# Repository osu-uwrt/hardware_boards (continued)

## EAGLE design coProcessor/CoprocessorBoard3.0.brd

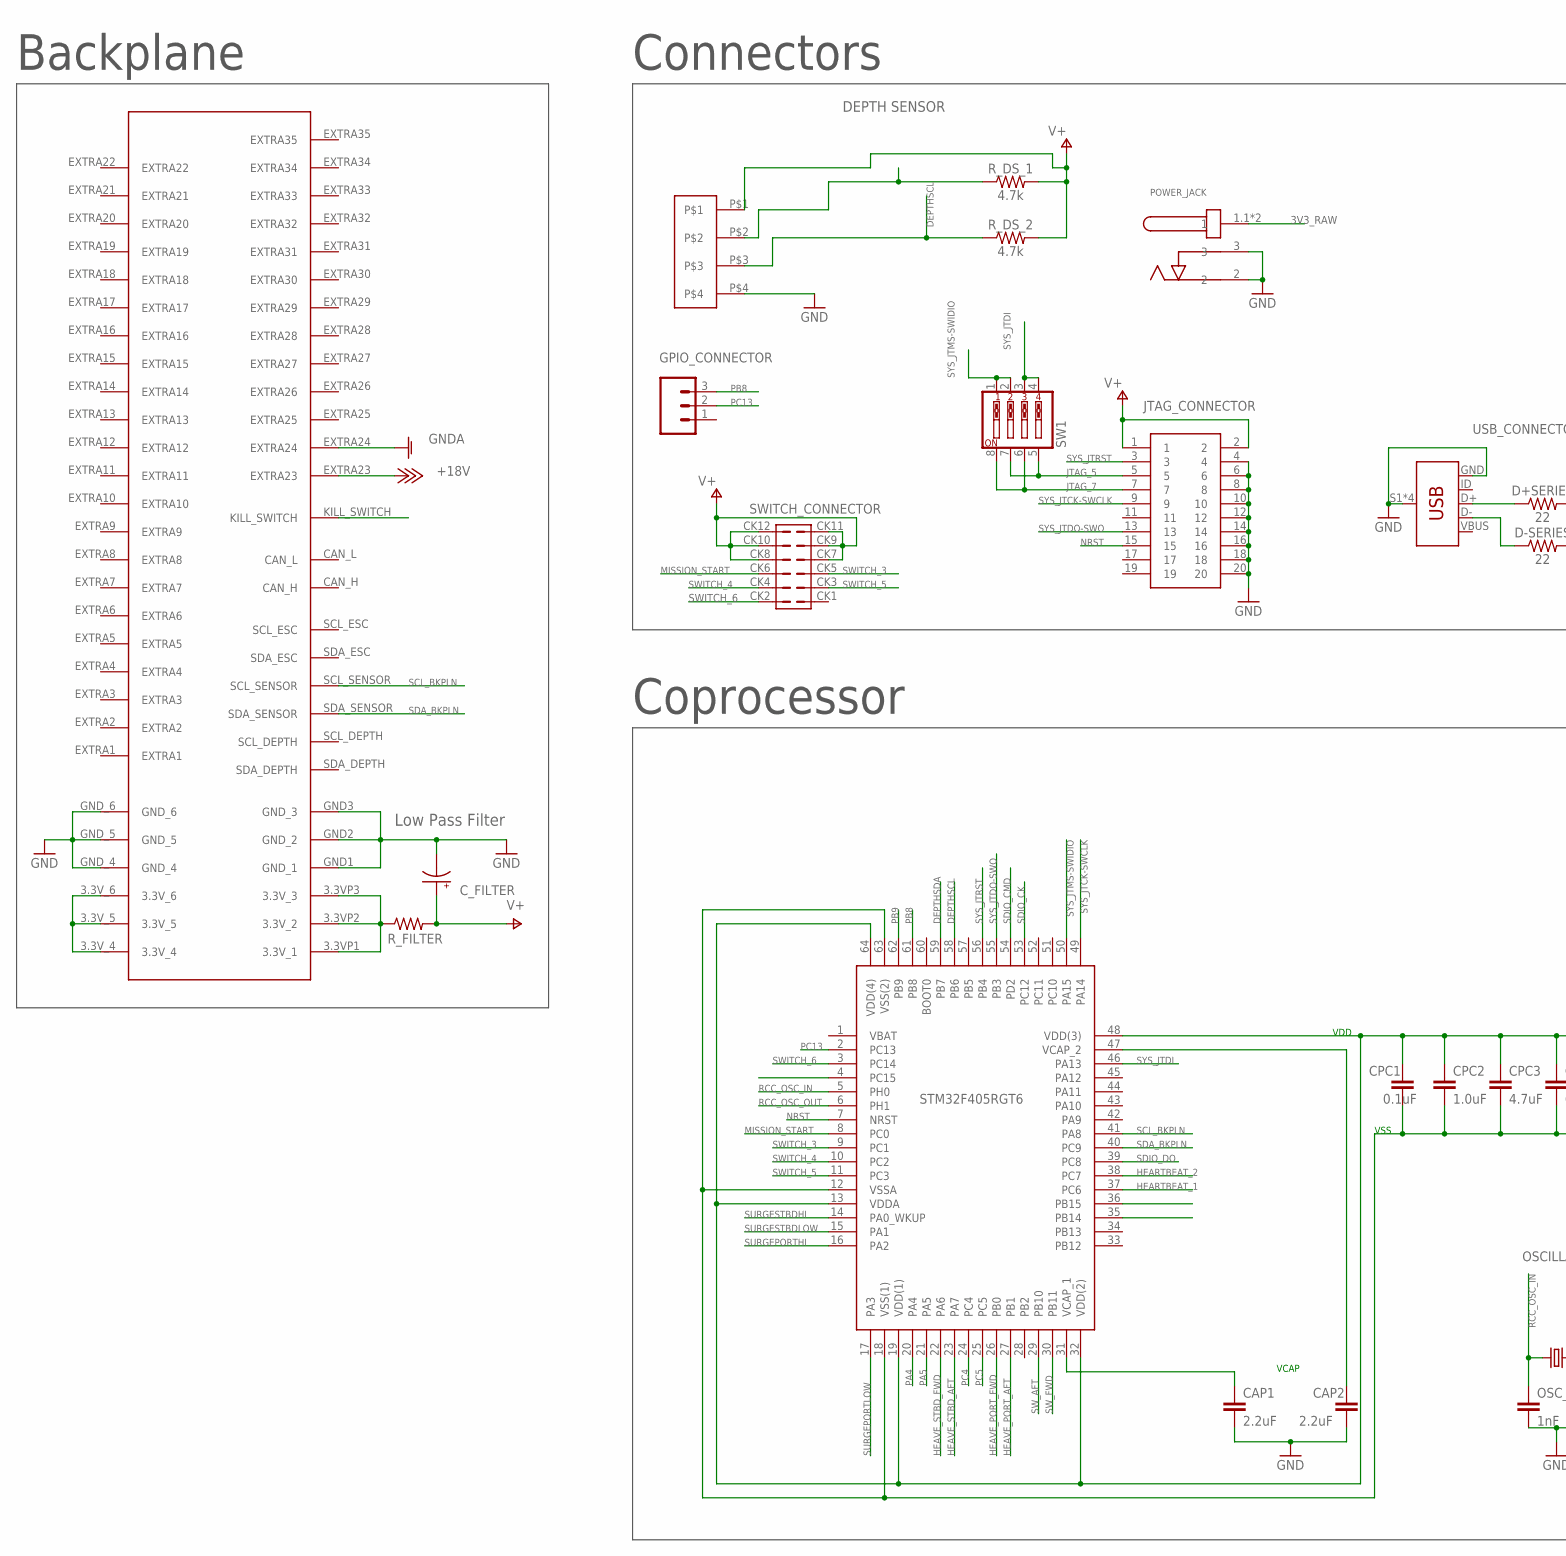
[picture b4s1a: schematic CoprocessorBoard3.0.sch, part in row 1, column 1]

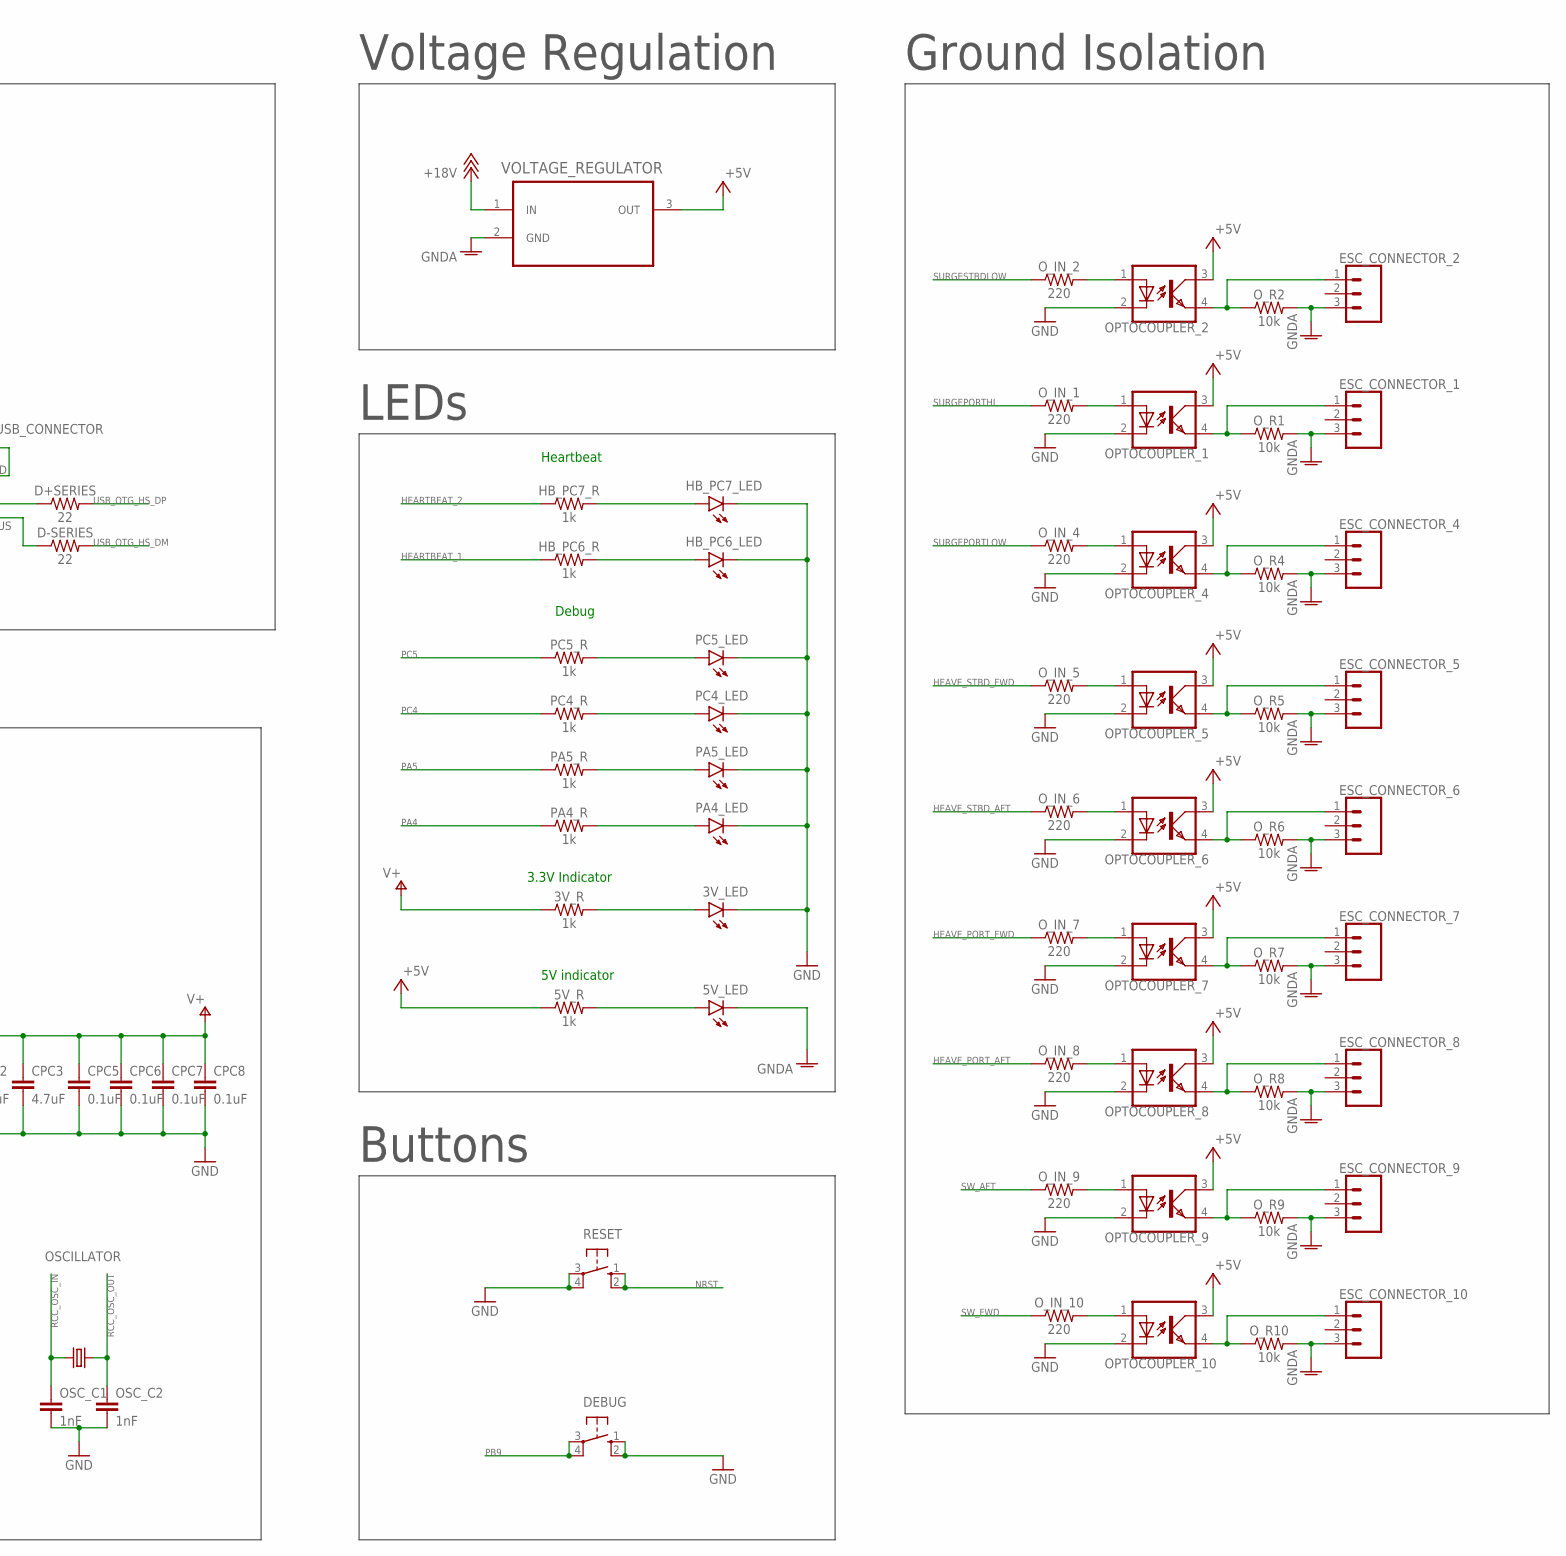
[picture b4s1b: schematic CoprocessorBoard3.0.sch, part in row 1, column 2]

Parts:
3V_LED, 5V_LED: WHITE; LED-0603
3V_R, 5V_R: 1k; AXIAL-0.3
CAP1, CAP2: 2.2uF; 0603
CPC1, CPC5, CPC6, CPC7, CPC8: 0.1uF; 0603
CPC2: 1.0uF; 0603
CPC3: 4.7uF; 0603
C_FILTER: CPOL-USE2-5; E2-5
D+SERIES: 22; AXIAL-0.3
D-SERIES: 22; AXIAL-0.3
DEBUG: 10-XX; B3F-10XX
ESC_CONNECTOR_1, ESC_CONNECTOR_2, ESC_CONNECTOR_4, ESC_CONNECTOR_5, ESC_CONNECTOR_6, ESC_CONNECTOR_7, ESC_CONNECTOR_8, ESC_CONNECTOR_9, ESC_CONNECTOR_10: 455-1750-1-ND; 1X03
GPIO_CONNECTOR: 455-1750-1-ND; 1X03
HB_PC6_LED, HB_PC7_LED: WHITE; LED-0603
HB_PC6_R, HB_PC7_R: 1k; AXIAL-0.3
IC1: STM32F405RGT6; QFP50P1200X1200X160-64N
JTAG_CONNECTOR: 30320-6002HB; SHDR20W81P254_2X10_3300X840X93
OPTOCOUPLER_1, OPTOCOUPLER_2, OPTOCOUPLER_4, OPTOCOUPLER_5, OPTOCOUPLER_6, OPTOCOUPLER_7, OPTOCOUPLER_8, OPTOCOUPLER_9, OPTOCOUPLER_10: SFH610; DIL04
OSCILLATOR: CRYSTALHC49S; HC49/S
OSC_C1, OSC_C2: 1nF; CAP-PTH-2.54
O_IN_1, O_IN_2, O_IN_4, O_IN_5, O_IN_6, O_IN_7, O_IN_8, O_IN_9, O_IN_10: 220; AXIAL-0.3
O_R1, O_R2, O_R4, O_R5, O_R6, O_R7, O_R8, O_R9, O_R10: 10k; AXIAL-0.3
PA4_LED, PA5_LED: WHITE; LED-0603
PA4_R, PA5_R: 1k; AXIAL-0.3
PC4_LED, PC5_LED: WHITE; LED-0603
PC4_R, PC5_R: 1k; AXIAL-0.3
POWER_JACK: PJ-002AH-SMT-TR; CUI_PJ-002AH-SMT-TR
RESET: 10-XX; B3F-10XX
R_DS_1, R_DS_2: 4.7k; AXIAL-0.3
R_FILTER: R-US_0204/7; 0204/7
SW1: SW_DIP-4; EDG-04
SWITCH_CONNECTOR: 105314-2112
U$1: 5530843; 5530843-6-BOARDFINGERS
U$2: NANOFIT_4PIN_STR
USB_CONNECTOR: USB_MINI-B_SMT; USB-MINIB
VOLTAGE_REGULATOR: L78M05CV; TO254P450X1020X1935-3P

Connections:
3V3: 3V_R.P$1 (1), CPC1.1, CPC2.1, CPC3.1, CPC5.1, CPC6.1, CPC7.1, CPC8.1, C_FILTER.+, IC1.13 (VDDA), IC1.19 (VDD(1)), IC1.32 (VDD(2)), IC1.48 (VDD(3)), IC1.64 (VDD(4)), JTAG_CONNECTOR.1, JTAG_CONNECTOR.2, R_DS_1.P$2 (2), R_DS_2.P$2 (2), R_FILTER.2, SWITCH_CONNECTOR.CK7, SWITCH_CONNECTOR.CK8, SWITCH_CONNECTOR.CK9, SWITCH_CONNECTOR.CK10, SWITCH_CONNECTOR.CK11, SWITCH_CONNECTOR.CK12, U$2.P$1
3V3_RAW: POWER_JACK.1.1 (1), POWER_JACK.1.2 (1), R_FILTER.1, U$1.3.3VP1 (3.3V_1), U$1.3.3VP2 (3.3V_2), U$1.3.3VP3 (3.3V_3), U$1.3.3V_4, U$1.3.3V_5, U$1.3.3V_6
+5V: 5V_R.P$1 (1), OPTOCOUPLER_1.3 (COL), OPTOCOUPLER_2.3 (COL), OPTOCOUPLER_4.3 (COL), OPTOCOUPLER_5.3 (COL), OPTOCOUPLER_6.3 (COL), OPTOCOUPLER_7.3 (COL), OPTOCOUPLER_8.3 (COL), OPTOCOUPLER_9.3 (COL), OPTOCOUPLER_10.3 (COL), VOLTAGE_REGULATOR.3 (OUT)
+18V: U$1.EXTRA23, VOLTAGE_REGULATOR.1 (IN)
D+CON: D+SERIES.P$1 (1), USB_CONNECTOR.D+
D-CON: D-SERIES.P$1 (1), USB_CONNECTOR.D-
DEPTHSCL: IC1.58 (PB6), R_DS_2.P$1 (1), U$2.P$3
DEPTHSDA: IC1.59 (PB7), R_DS_1.P$1 (1), U$2.P$2
GND: 3V_LED.C, CAP1.2, CAP2.2, CPC1.2, CPC2.2, CPC3.2, CPC5.2, CPC6.2, CPC7.2, CPC8.2, C_FILTER.-, DEBUG.1 (S), DEBUG.2 (S1), HB_PC6_LED.C, HB_PC7_LED.C, IC1.12 (VSSA), IC1.18 (VSS(1)), IC1.63 (VSS(2)), JTAG_CONNECTOR.4, JTAG_CONNECTOR.6, JTAG_CONNECTOR.8, JTAG_CONNECTOR.10, JTAG_CONNECTOR.12, JTAG_CONNECTOR.14, JTAG_CONNECTOR.16, JTAG_CONNECTOR.18, JTAG_CONNECTOR.20, OPTOCOUPLER_1.2 (C), OPTOCOUPLER_2.2 (C), OPTOCOUPLER_4.2 (C), OPTOCOUPLER_5.2 (C), OPTOCOUPLER_6.2 (C), OPTOCOUPLER_7.2 (C), OPTOCOUPLER_8.2 (C), OPTOCOUPLER_9.2 (C), OPTOCOUPLER_10.2 (C), OSC_C1.2, OSC_C2.2, PA4_LED.C, PA5_LED.C, PC4_LED.C, PC5_LED.C, POWER_JACK.2, POWER_JACK.3, RESET.3, RESET.4 (P1), U$1.GND1 (GND_1), U$1.GND2 (GND_2), U$1.GND3 (GND_3), U$1.GND_4, U$1.GND_5, U$1.GND_6, U$2.P$4, USB_CONNECTOR.GND, USB_CONNECTOR.S1 (SHIELD), USB_CONNECTOR.S2 (SHIELD), USB_CONNECTOR.S3 (SHIELD), USB_CONNECTOR.S4 (SHIELD)
GNDBAT: 5V_LED.C, ESC_CONNECTOR_1.3, ESC_CONNECTOR_2.3, ESC_CONNECTOR_4.3, ESC_CONNECTOR_5.3, ESC_CONNECTOR_6.3, ESC_CONNECTOR_7.3, ESC_CONNECTOR_8.3, ESC_CONNECTOR_9.3, ESC_CONNECTOR_10.3, O_R1.P$2 (2), O_R2.P$2 (2), O_R4.P$2 (2), O_R5.P$2 (2), O_R6.P$2 (2), O_R7.P$2 (2), O_R8.P$2 (2), O_R9.P$2 (2), O_R10.P$2 (2), U$1.EXTRA24, VOLTAGE_REGULATOR.2 (GND)
HEARTBEAT_1: HB_PC6_R.P$1 (1), IC1.37 (PC6)
HEARTBEAT_2: HB_PC7_R.P$1 (1), IC1.38 (PC7)
HEAVE_PORT_AFT: IC1.27 (PB1), O_IN_8.P$1 (1)
HEAVE_PORT_FWD: IC1.26 (PB0), O_IN_7.P$1 (1)
HEAVE_STBD_AFT: IC1.23 (PA7), O_IN_6.P$1 (1)
HEAVE_STBD_FWD: IC1.22 (PA6), O_IN_5.P$1 (1)
JTAG_5: JTAG_CONNECTOR.5, SW1.5, SW1.7
JTAG_7: JTAG_CONNECTOR.7, SW1.6, SW1.8
KILL_SWITCH: IC1.4 (PC15), U$1.KILL_SWITCH
MISSION_START: IC1.8 (PC0), SWITCH_CONNECTOR.CK6
unnamed: ESC_CONNECTOR_1.1, OPTOCOUPLER_1.4 (EMIT), O_R1.P$1 (1)
unnamed: ESC_CONNECTOR_2.1, OPTOCOUPLER_2.4 (EMIT), O_R2.P$1 (1)
unnamed: OPTOCOUPLER_1.1 (A), O_IN_1.P$2 (2)
unnamed: ESC_CONNECTOR_4.1, OPTOCOUPLER_4.4 (EMIT), O_R4.P$1 (1)
unnamed: ESC_CONNECTOR_5.1, OPTOCOUPLER_5.4 (EMIT), O_R5.P$1 (1)
unnamed: ESC_CONNECTOR_6.1, OPTOCOUPLER_6.4 (EMIT), O_R6.P$1 (1)
unnamed: ESC_CONNECTOR_7.1, OPTOCOUPLER_7.4 (EMIT), O_R7.P$1 (1)
unnamed: ESC_CONNECTOR_8.1, OPTOCOUPLER_8.4 (EMIT), O_R8.P$1 (1)
unnamed: ESC_CONNECTOR_9.1, OPTOCOUPLER_9.4 (EMIT), O_R9.P$1 (1)
unnamed: ESC_CONNECTOR_10.1, OPTOCOUPLER_10.4 (EMIT), O_R10.P$1 (1)
unnamed: OPTOCOUPLER_10.1 (A), O_IN_10.P$2 (2)
unnamed: OPTOCOUPLER_9.1 (A), O_IN_9.P$2 (2)
unnamed: OPTOCOUPLER_8.1 (A), O_IN_8.P$2 (2)
unnamed: OPTOCOUPLER_7.1 (A), O_IN_7.P$2 (2)
unnamed: OPTOCOUPLER_6.1 (A), O_IN_6.P$2 (2)
unnamed: OPTOCOUPLER_5.1 (A), O_IN_5.P$2 (2)
unnamed: OPTOCOUPLER_4.1 (A), O_IN_4.P$2 (2)
unnamed: OPTOCOUPLER_2.1 (A), O_IN_2.P$2 (2)
unnamed: HB_PC6_LED.A, HB_PC6_R.P$2 (2)
unnamed: HB_PC7_LED.A, HB_PC7_R.P$2 (2)
unnamed: PC5_LED.A, PC5_R.P$2 (2)
unnamed: PC4_LED.A, PC4_R.P$2 (2)
unnamed: PA5_LED.A, PA5_R.P$2 (2)
unnamed: PA4_LED.A, PA4_R.P$2 (2)
unnamed: 5V_LED.A, 5V_R.P$2 (2)
unnamed: 3V_LED.A, 3V_R.P$2 (2)
NRST: IC1.7 (NRST), JTAG_CONNECTOR.15, RESET.1 (S), RESET.2 (S1)
PA4: IC1.20 (PA4), PA4_R.P$1 (1)
PA5: IC1.21 (PA5), PA5_R.P$1 (1)
PB8: GPIO_CONNECTOR.3, IC1.61 (PB8)
PB9: DEBUG.3, DEBUG.4 (P1), IC1.62 (PB9)
PC4: IC1.24 (PC4), PC4_R.P$1 (1)
PC5: IC1.25 (PC5), PC5_R.P$1 (1)
PC13: GPIO_CONNECTOR.2, IC1.2 (PC13)
RCC_OSC_IN: IC1.5 (PH0), OSCILLATOR.1, OSC_C1.1
RCC_OSC_OUT: IC1.6 (PH1), OSCILLATOR.2, OSC_C2.1
SCL_BKPLN: IC1.41 (PA8), U$1.SCL_SENSOR
SDA_BKPLN: IC1.40 (PC9), U$1.SDA_SENSOR
SDIO_CK: IC1.53 (PC12)
SDIO_CMD: IC1.54 (PD2)
SDIO_DO: IC1.39 (PC8)
SURGEPORTHI: IC1.16 (PA2), O_IN_1.P$1 (1)
SURGEPORTLOW: IC1.17 (PA3), O_IN_4.P$1 (1)
SURGESTBDHI: IC1.14 (PA0_WKUP)
SURGESTBDLOW: IC1.15 (PA1), O_IN_2.P$1 (1)
SWITCH_3: IC1.9 (PC1), SWITCH_CONNECTOR.CK5
SWITCH_4: IC1.10 (PC2), SWITCH_CONNECTOR.CK4
SWITCH_5: IC1.11 (PC3), SWITCH_CONNECTOR.CK3
SWITCH_6: IC1.3 (PC14), SWITCH_CONNECTOR.CK2
SW_AFT: IC1.29 (PB10), O_IN_9.P$1 (1)
SW_FWD: IC1.30 (PB11), O_IN_10.P$1 (1)
SYS_JTCK-SWCLK: IC1.49 (PA14), JTAG_CONNECTOR.9
SYS_JTDI: IC1.46 (PA13), SW1.3, SW1.4
SYS_JTDO-SWO: IC1.55 (PB3), JTAG_CONNECTOR.13
SYS_JTMS-SWIDIO: IC1.50 (PA15), SW1.1, SW1.2
SYS_JTRST: IC1.56 (PB4), JTAG_CONNECTOR.3
USB_OTG_HS_DM: D-SERIES.P$2 (2), IC1.35 (PB14)
USB_OTG_HS_DP: D+SERIES.P$2 (2), IC1.36 (PB15)
VBUS: USB_CONNECTOR.VBUS
VCAP1: CAP1.1, IC1.31 (VCAP_1)
VCAP2: CAP2.1, IC1.47 (VCAP_2)

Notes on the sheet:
Connectors
Voltage Regulation
Ground Isolation
Coprocessor
VCAP
VDD
VSS
Backplane
LEDs
Heartbeat
Debug
5V indicator
3.3V Indicator
Buttons
DEPTH SENSOR
Low Pass Filter

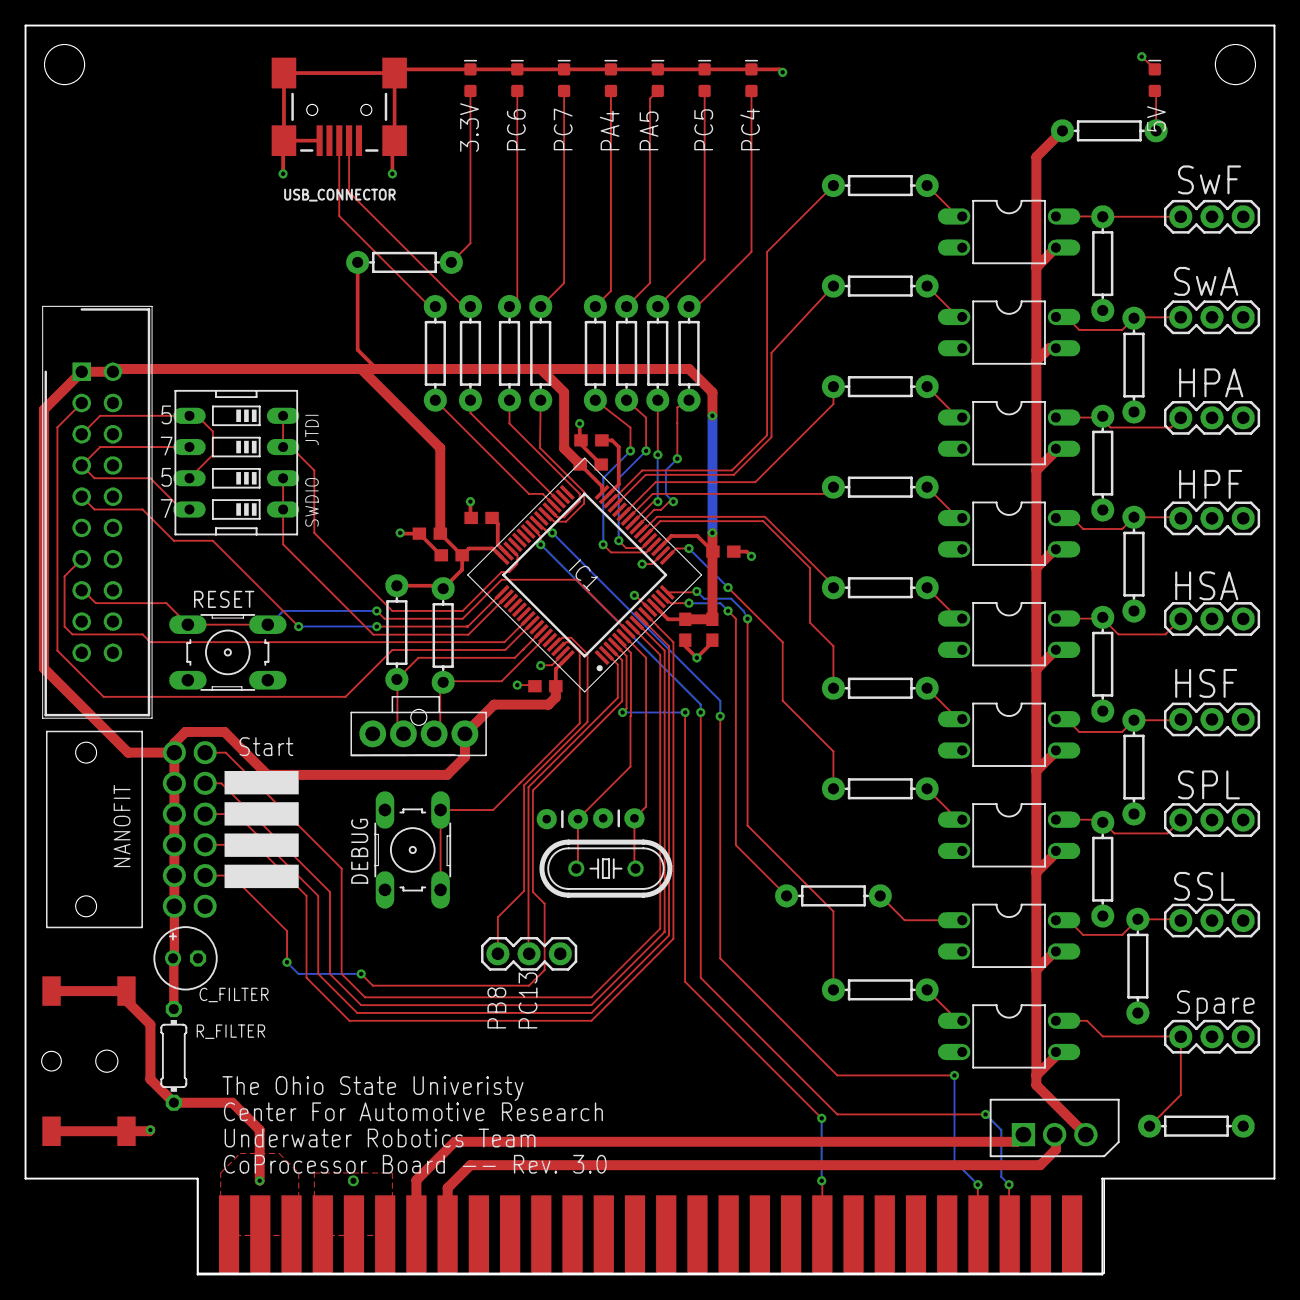
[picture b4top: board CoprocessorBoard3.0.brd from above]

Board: 2 copper layers, 101.6 x 101.6 mm, 82 parts (0 on the bottom side), 76 nets.

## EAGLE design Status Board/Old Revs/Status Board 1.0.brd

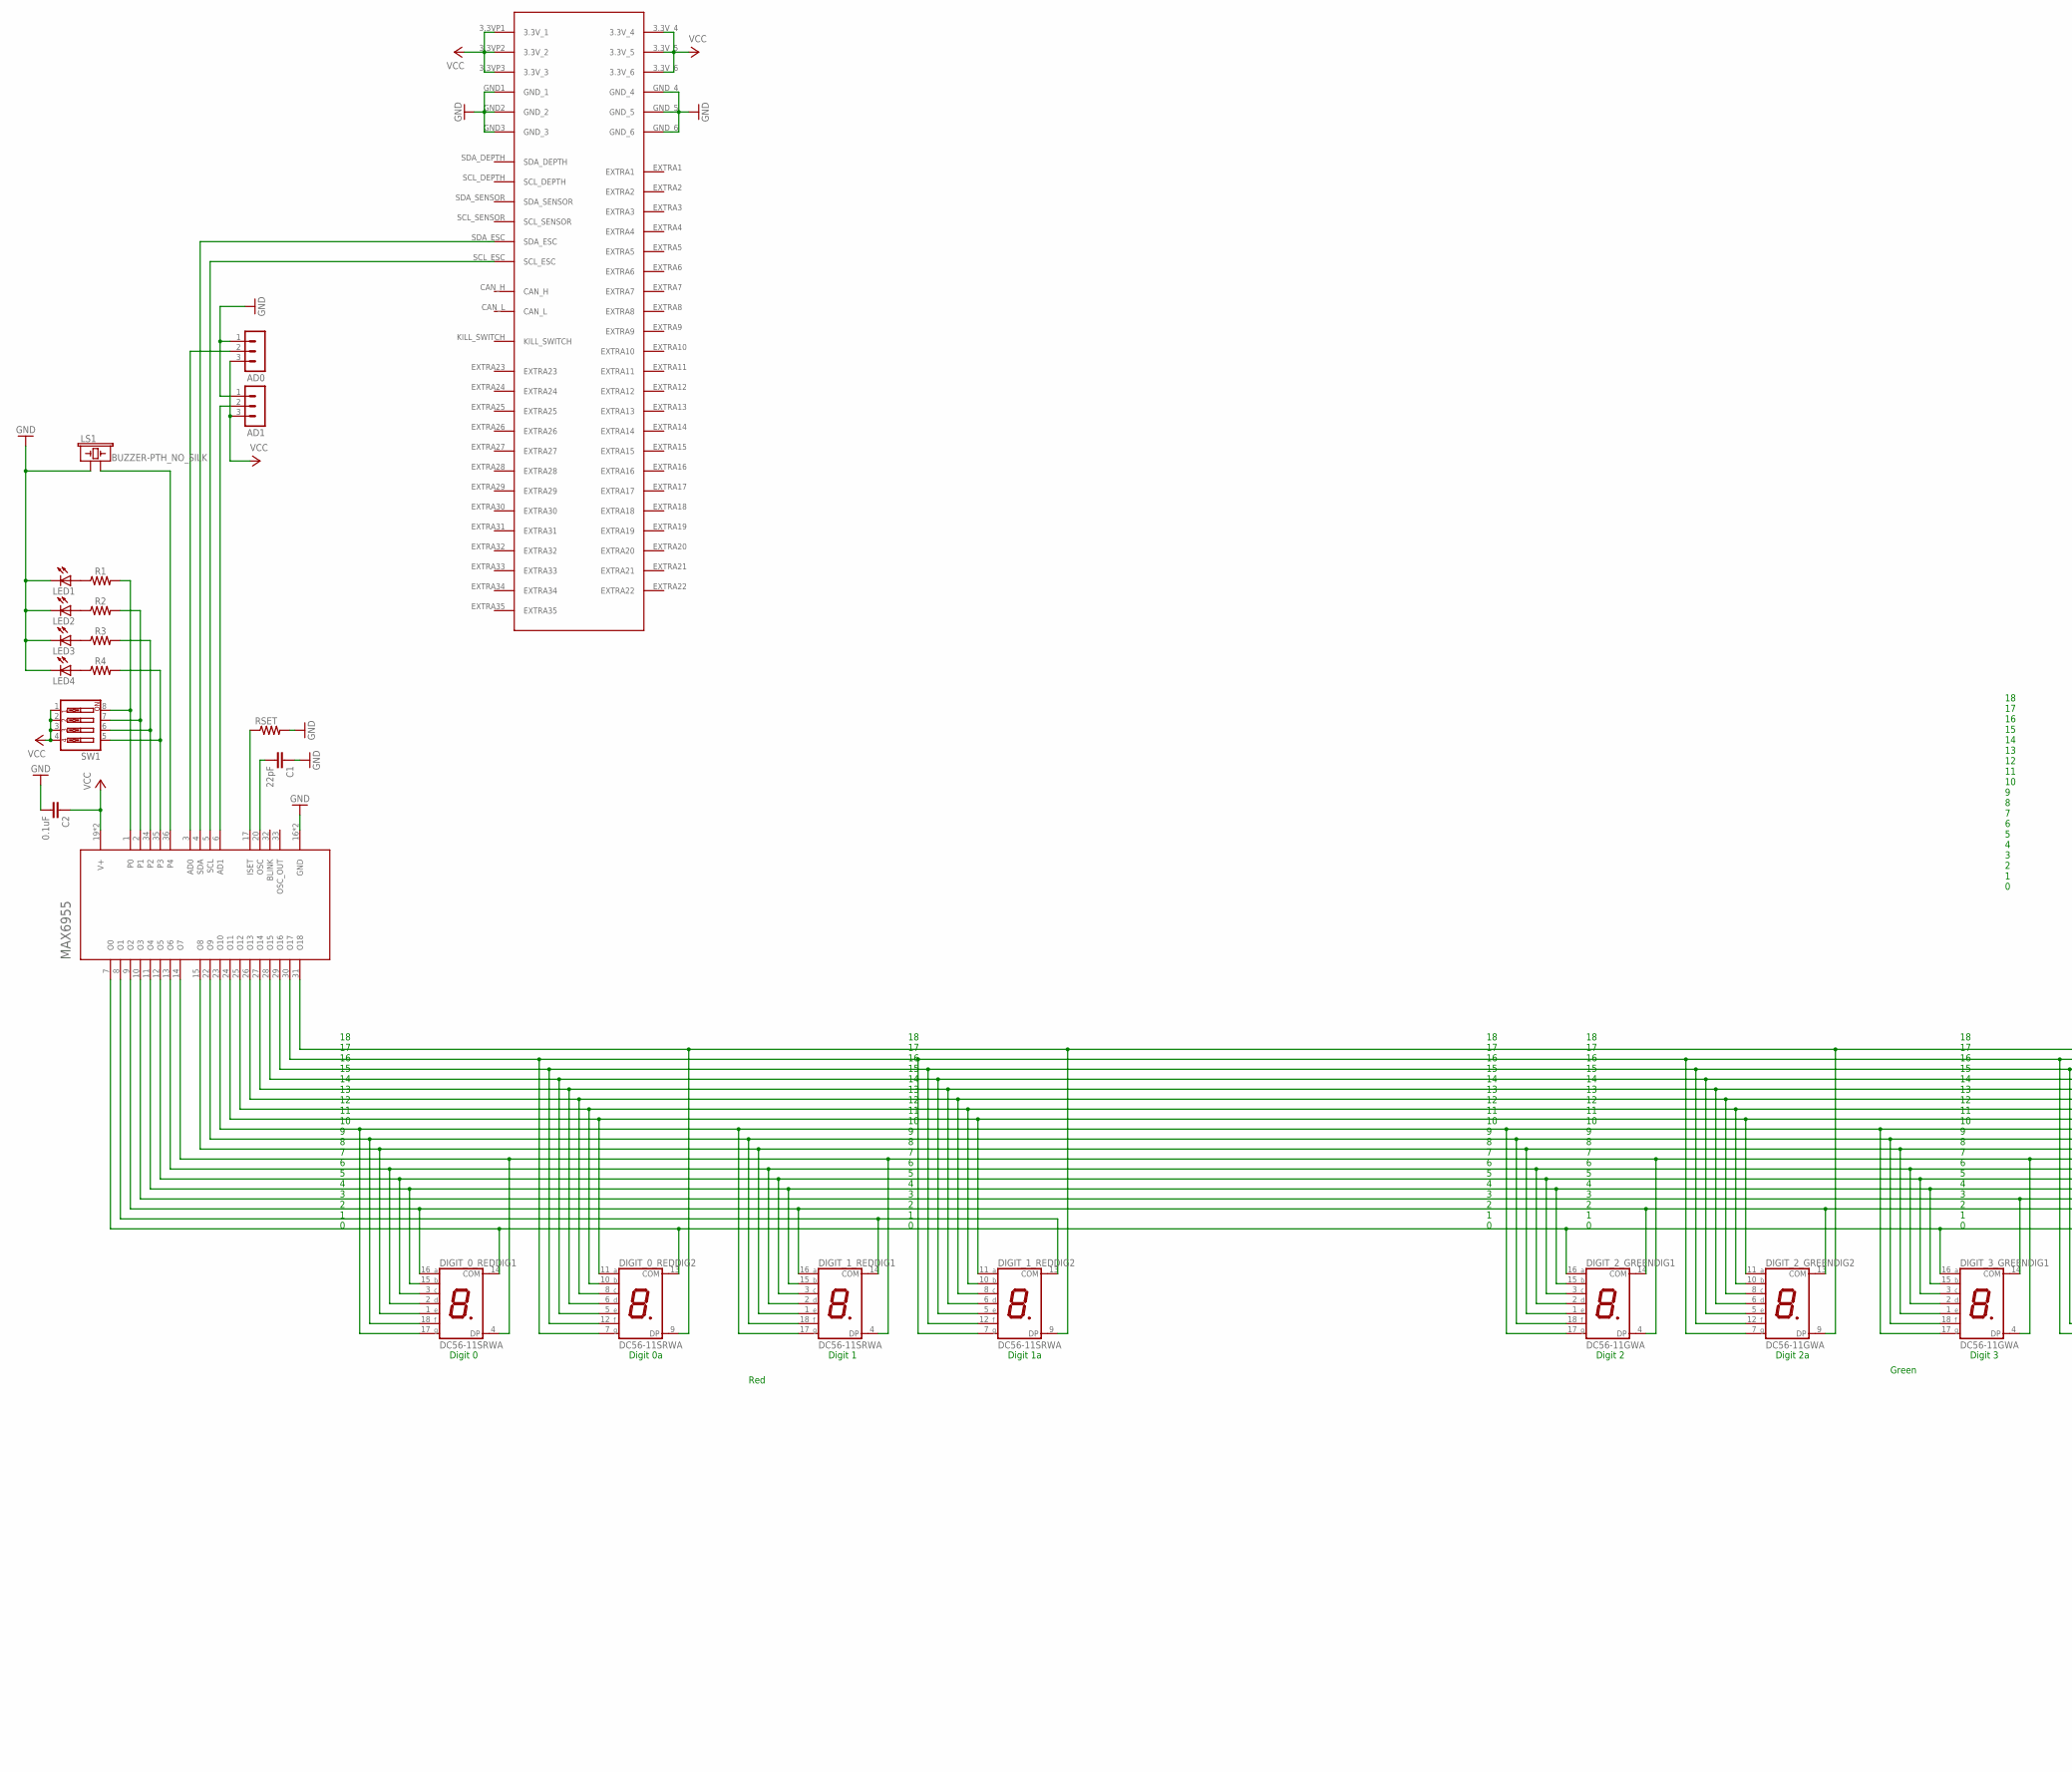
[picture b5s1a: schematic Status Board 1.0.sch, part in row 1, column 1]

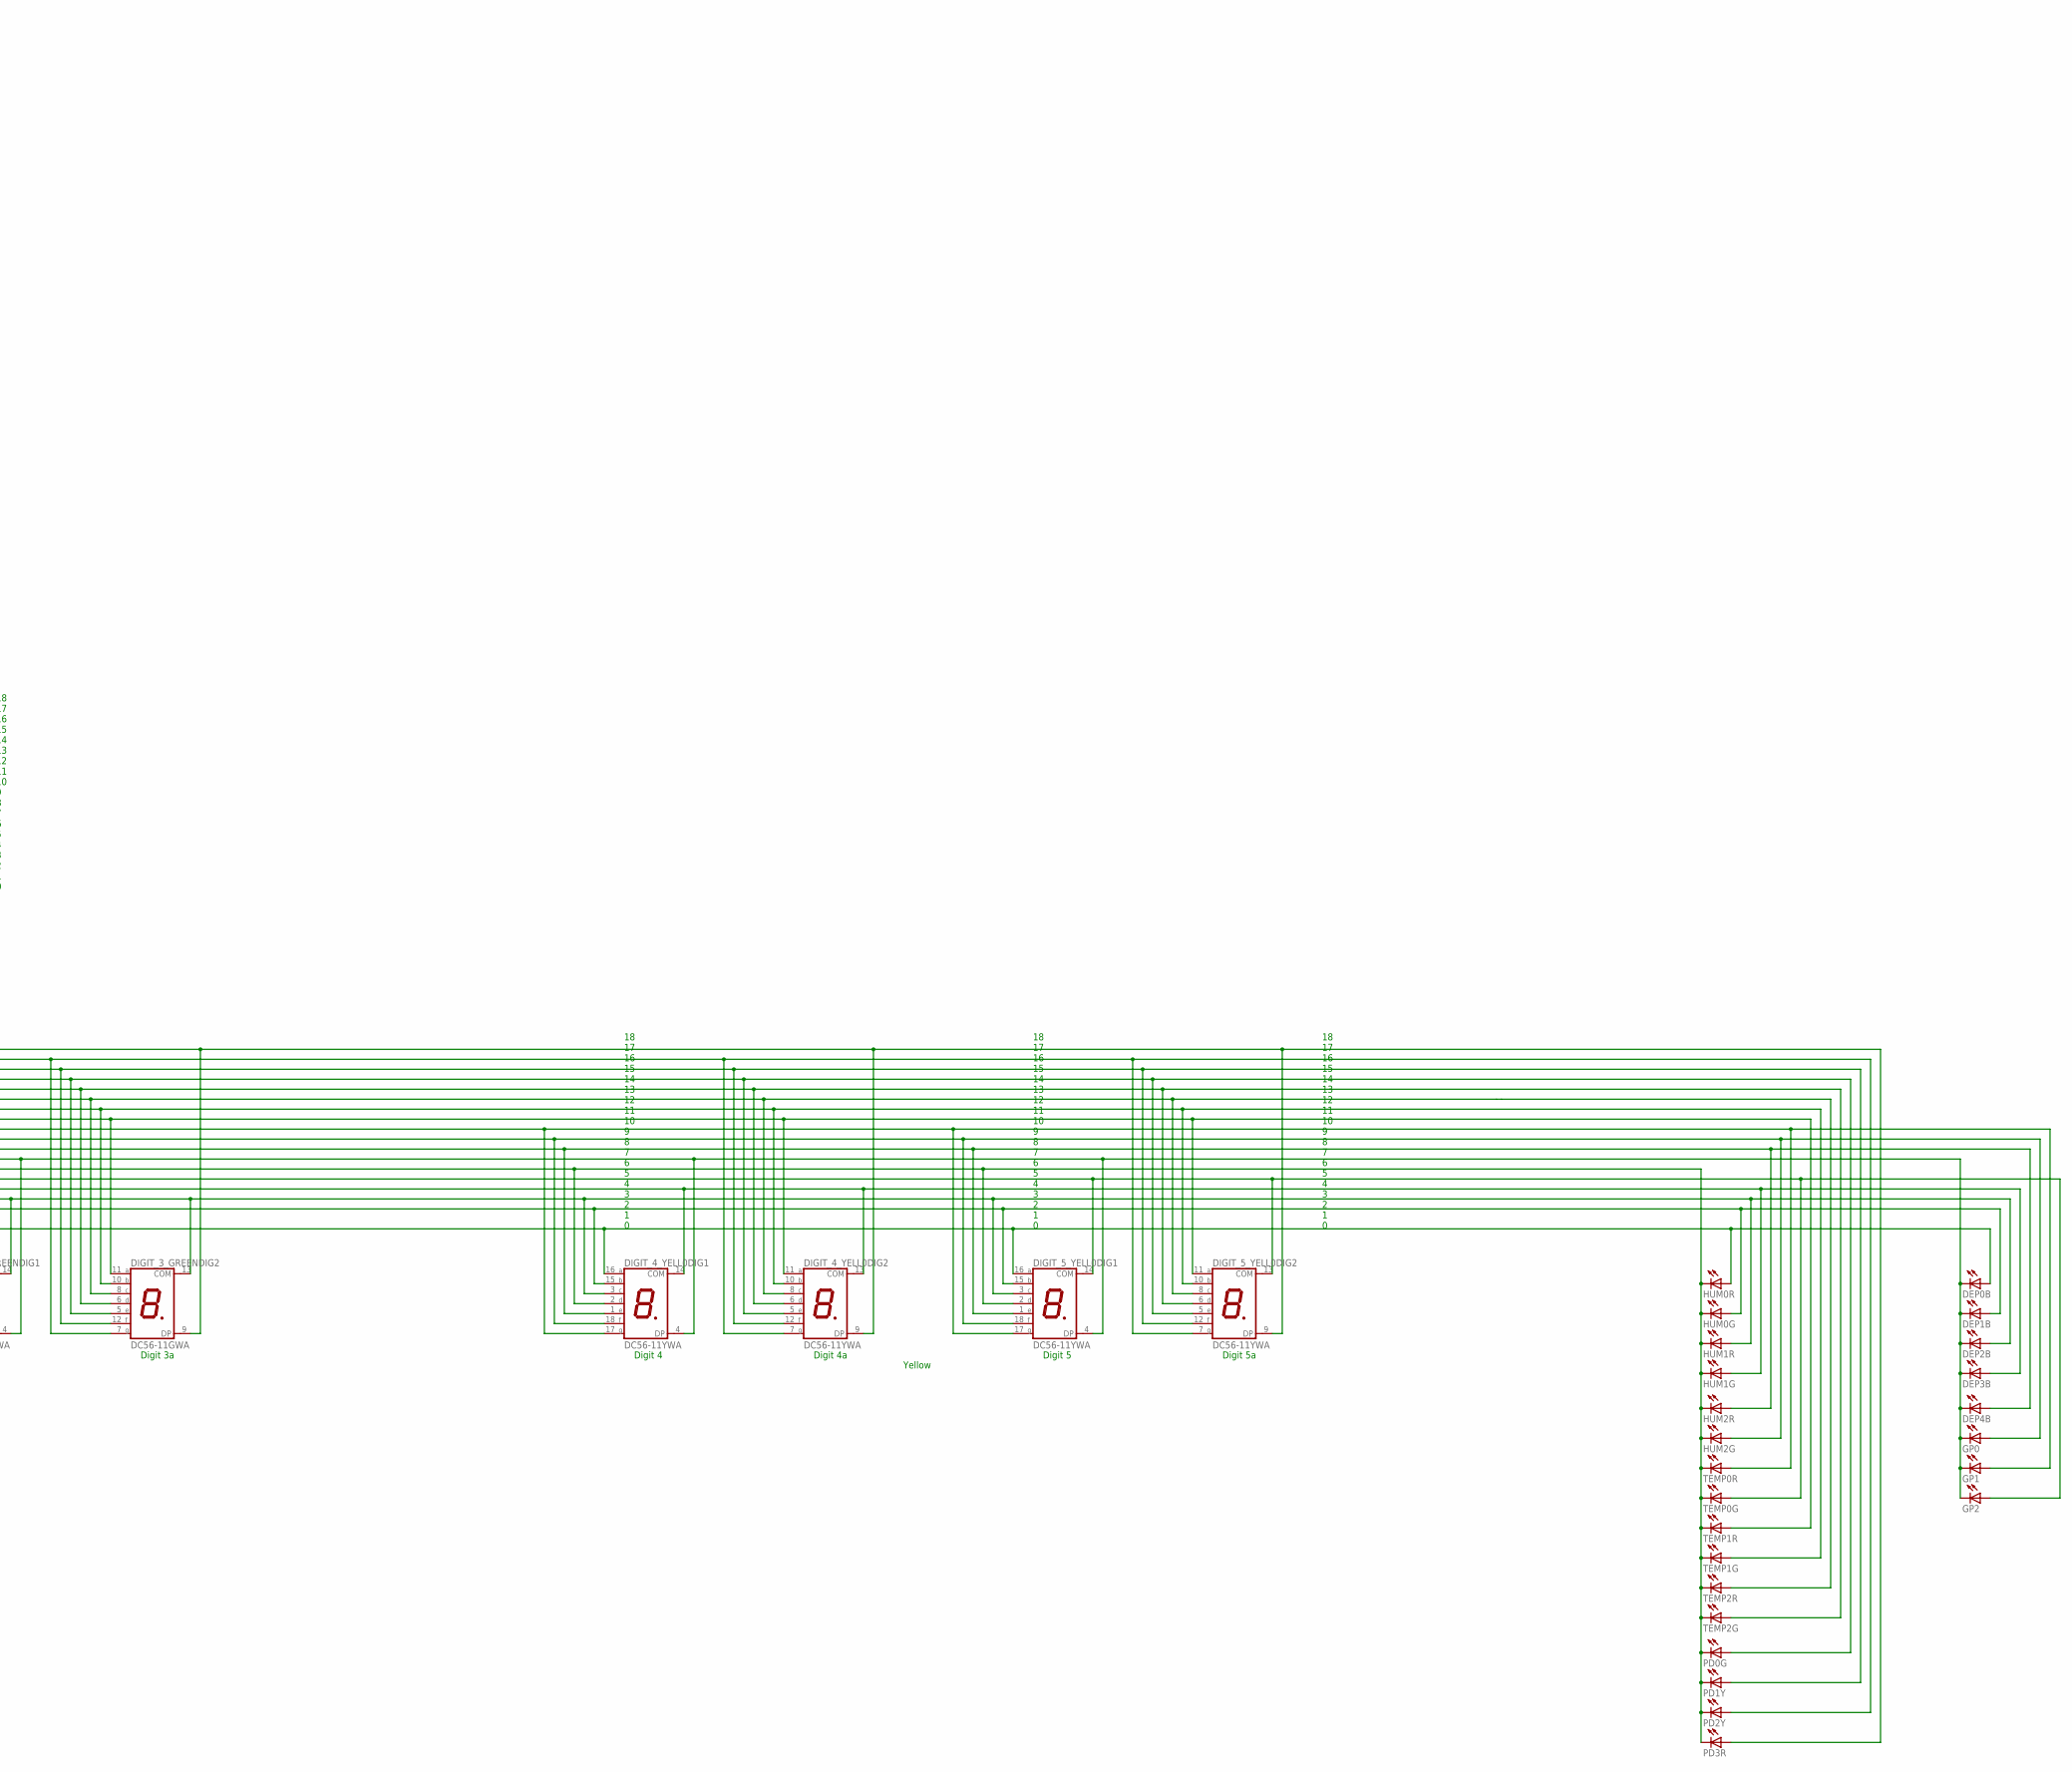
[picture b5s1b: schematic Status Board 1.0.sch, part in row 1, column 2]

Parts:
AD0, AD1: MA03-1
C1: 22pF; CAP-PTH-2.54
C2: 0.1uF; CAP-PTH-SMALL-KIT
DEP0B, DEP1B, DEP2B, DEP3B, DEP4B: LED3MM
DIGIT_0_RED, DIGIT_1_RED: DC56-11SRWA; DA56
DIGIT_2_GREEN, DIGIT_3_GREEN: DC56-11GWA; DA56
DIGIT_4_YELL0, DIGIT_5_YELL0: DC56-11YWA; DA56
GP0, GP1, GP2: LED3MM
HUM0G, HUM0R, HUM1G, HUM1R, HUM2G, HUM2R: LED3MM
LED1, LED2, LED3, LED4: LED_ESML0603; LED_SML0603
LS1: BUZZER-PTH_NO_SILK; BUZZER-12MM-NS
MAX6955: MAX6955; SSOP36
PD0G, PD1Y, PD2Y, PD3R: LED3MM
R1, R2, R3, R4: 68OHM-0603-1/10W-1%; 0603
RSET: R-US_0207/12; 0207/12
SW1: SW_DIP-4; EDG-04
TEMP0G, TEMP0R, TEMP1G, TEMP1R, TEMP2G, TEMP2R: LED3MM
U$2: 5530843; 5530843-6-BOARDFINGERS

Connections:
GND: AD0.1, AD1.1, C1.1, C2.2, LED1.C, LED2.C, LED3.C, LED4.C, LS1.+ (1), MAX6955.16 (GND), MAX6955.18 (GND), RSET.2, U$2.GND1 (GND_1), U$2.GND2 (GND_2), U$2.GND3 (GND_3), U$2.GND_4, U$2.GND_5, U$2.GND_6
unnamed: LED1.A, R1.1
unnamed: MAX6955.5 (SCL), U$2.SCL_ESC
unnamed: LED2.A, R2.1
unnamed: MAX6955.1 (P0), R1.2, SW1.8
unnamed: MAX6955.2 (P1), R2.2, SW1.7
unnamed: MAX6955.34 (P2), R3.2, SW1.6
unnamed: MAX6955.35 (P3), R4.2, SW1.5
unnamed: LS1.- (2), MAX6955.36 (P4)
unnamed: LED3.A, R3.1
unnamed: LED4.A, R4.1
unnamed: AD0.2, MAX6955.3 (AD0)
unnamed: AD1.2, MAX6955.6 (AD1)
unnamed: C1.2, MAX6955.20 (OSC)
unnamed: DEP4B.A, DIGIT_0_RED.1 (E), DIGIT_1_RED.1 (E), DIGIT_2_GREEN.1 (E), DIGIT_3_GREEN.1 (E), DIGIT_4_YELL0.1 (E), DIGIT_5_YELL0.1 (E), HUM2R.A, MAX6955.15 (O8)
unnamed: DEP0B.A, DIGIT_0_RED.13 (COM), DIGIT_0_RED.14 (COM), DIGIT_2_GREEN.16 (A), DIGIT_3_GREEN.16 (A), DIGIT_4_YELL0.16 (A), DIGIT_5_YELL0.16 (A), HUM0R.A, MAX6955.7 (O0)
unnamed: DIGIT_1_RED.13 (COM), DIGIT_1_RED.14 (COM), MAX6955.8 (O1)
unnamed: DEP1B.A, DIGIT_0_RED.16 (A), DIGIT_1_RED.16 (A), DIGIT_2_GREEN.13 (COM), DIGIT_2_GREEN.14 (COM), DIGIT_4_YELL0.15 (B), DIGIT_5_YELL0.15 (B), HUM0G.A, MAX6955.9 (O2)
unnamed: DEP2B.A, DIGIT_3_GREEN.13 (COM), DIGIT_3_GREEN.14 (COM), DIGIT_4_YELL0.3 (C), DIGIT_5_YELL0.3 (C), HUM1R.A, MAX6955.10 (O3)
unnamed: DEP3B.A, DIGIT_0_RED.15 (B), DIGIT_1_RED.15 (B), DIGIT_2_GREEN.15 (B), DIGIT_3_GREEN.15 (B), DIGIT_4_YELL0.13 (COM), DIGIT_4_YELL0.14 (COM), HUM1G.A, MAX6955.11 (O4)
unnamed: DIGIT_0_RED.3 (C), DIGIT_1_RED.3 (C), DIGIT_2_GREEN.3 (C), DIGIT_3_GREEN.3 (C), DIGIT_5_YELL0.13 (COM), DIGIT_5_YELL0.14 (COM), GP2.A, MAX6955.12 (O5), TEMP0G.A
unnamed: DIGIT_0_RED.18 (F), DIGIT_1_RED.18 (F), DIGIT_2_GREEN.18 (F), DIGIT_3_GREEN.18 (F), DIGIT_4_YELL0.18 (F), DIGIT_5_YELL0.18 (F), GP0.A, HUM2G.A, MAX6955.22 (O9)
unnamed: DIGIT_0_RED.17 (G), DIGIT_1_RED.17 (G), DIGIT_2_GREEN.17 (G), DIGIT_3_GREEN.17 (G), DIGIT_4_YELL0.17 (G), DIGIT_5_YELL0.17 (G), GP1.A, MAX6955.23 (O10), TEMP0R.A
unnamed: DIGIT_0_RED.11 (A), DIGIT_1_RED.11 (A), DIGIT_2_GREEN.11 (A), DIGIT_3_GREEN.11 (A), DIGIT_4_YELL0.11 (A), DIGIT_5_YELL0.11 (A), MAX6955.24 (O11), TEMP1R.A
unnamed: DIGIT_0_RED.10 (B), DIGIT_1_RED.10 (B), DIGIT_2_GREEN.10 (B), DIGIT_3_GREEN.10 (B), DIGIT_4_YELL0.10 (B), DIGIT_5_YELL0.10 (B), MAX6955.25 (O12), TEMP1G.A
unnamed: DIGIT_0_RED.2 (D), DIGIT_1_RED.2 (D), DIGIT_2_GREEN.2 (D), DIGIT_3_GREEN.2 (D), DIGIT_4_YELL0.2 (D), DIGIT_5_YELL0.2 (D), HUM0G.K (C), HUM0R.K (C), HUM1G.K (C), HUM1R.K (C), HUM2G.K (C), HUM2R.K (C), MAX6955.13 (O6), PD0G.K (C), PD1Y.K (C), PD2Y.K (C), PD3R.K (C), TEMP0G.K (C), TEMP0R.K (C), TEMP1G.K (C), TEMP1R.K (C), TEMP2G.K (C), TEMP2R.K (C)
unnamed: DIGIT_0_RED.6 (D), DIGIT_1_RED.6 (D), DIGIT_2_GREEN.6 (D), DIGIT_3_GREEN.6 (D), DIGIT_4_YELL0.6 (D), DIGIT_5_YELL0.6 (D), MAX6955.27 (O14), TEMP2G.A
unnamed: DIGIT_0_RED.5 (E), DIGIT_1_RED.5 (E), DIGIT_2_GREEN.5 (E), DIGIT_3_GREEN.5 (E), DIGIT_4_YELL0.5 (E), DIGIT_5_YELL0.5 (E), MAX6955.28 (O15), PD0G.A
unnamed: DIGIT_0_RED.12 (F), DIGIT_1_RED.12 (F), DIGIT_2_GREEN.12 (F), DIGIT_3_GREEN.12 (F), DIGIT_4_YELL0.12 (F), DIGIT_5_YELL0.12 (F), MAX6955.29 (O16), PD1Y.A
unnamed: DIGIT_0_RED.7 (G), DIGIT_1_RED.7 (G), DIGIT_2_GREEN.7 (G), DIGIT_3_GREEN.7 (G), DIGIT_4_YELL0.7 (G), DIGIT_5_YELL0.7 (G), MAX6955.30 (O17), PD2Y.A
unnamed: DIGIT_0_RED.9 (DP), DIGIT_1_RED.9 (DP), DIGIT_2_GREEN.9 (DP), DIGIT_3_GREEN.9 (DP), DIGIT_4_YELL0.9 (DP), DIGIT_5_YELL0.9 (DP), MAX6955.31 (O18), PD3R.A
unnamed: DIGIT_0_RED.8 (C), DIGIT_1_RED.8 (C), DIGIT_2_GREEN.8 (C), DIGIT_3_GREEN.8 (C), DIGIT_4_YELL0.8 (C), DIGIT_5_YELL0.8 (C), MAX6955.26 (O13), TEMP2R.A
unnamed: MAX6955.4 (SDA), U$2.SDA_ESC
unnamed: MAX6955.17 (ISET), RSET.1
unnamed: DEP0B.K (C), DEP1B.K (C), DEP2B.K (C), DEP3B.K (C), DEP4B.K (C), DIGIT_0_RED.4 (DP), DIGIT_1_RED.4 (DP), DIGIT_2_GREEN.4 (DP), DIGIT_3_GREEN.4 (DP), DIGIT_4_YELL0.4 (DP), DIGIT_5_YELL0.4 (DP), GP0.K (C), GP1.K (C), GP2.K (C), MAX6955.14 (O7)
VCC: AD0.3, AD1.3, C2.1, MAX6955.19 (V+), MAX6955.21 (V+), SW1.1, SW1.2, SW1.3, SW1.4, U$2.3.3VP1 (3.3V_1), U$2.3.3VP2 (3.3V_2), U$2.3.3VP3 (3.3V_3), U$2.3.3V_4, U$2.3.3V_5, U$2.3.3V_6

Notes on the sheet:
Green
Red
Yellow
Digit 0
Digit 0a
18 17 16 15 14 13 12 11 10 9 8 7 6 5 4 3 2 1 0
Digit 1
Digit 1a
Digit 2
Digit 2a
Digit 3
Digit 3a
Digit 4
Digit 4a
Digit 5
Digit 5a

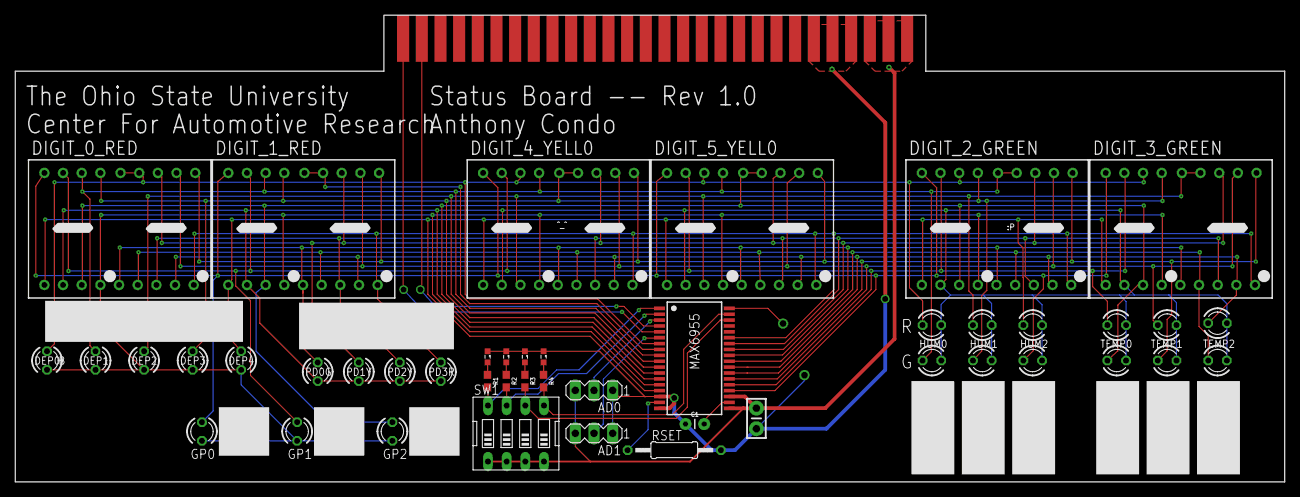
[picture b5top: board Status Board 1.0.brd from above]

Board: 2 copper layers, 172.7 x 63.5 mm, 47 parts (0 on the bottom side), 36 nets.
